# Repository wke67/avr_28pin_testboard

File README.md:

## AVR 28-Pin Test Board

The board can use a 300/400 mil ZIF socket for Mega AVR devices in dual inline package, eg. avr64dd28. All dx, ex 28-pin DIL devices have identical pin-out. The board provides:
- USB-C 12 Mbit interface
- dual UART interface for simultaneous serial and UPDI access.
- 3.3v, 500mA power supply from USB
- reset circuitry compatible with Arduino IDE and HV UPDI
- status LED on port PA6
- user switch on port PA7
- 32768 Hz crystal connected to PF0/PF1

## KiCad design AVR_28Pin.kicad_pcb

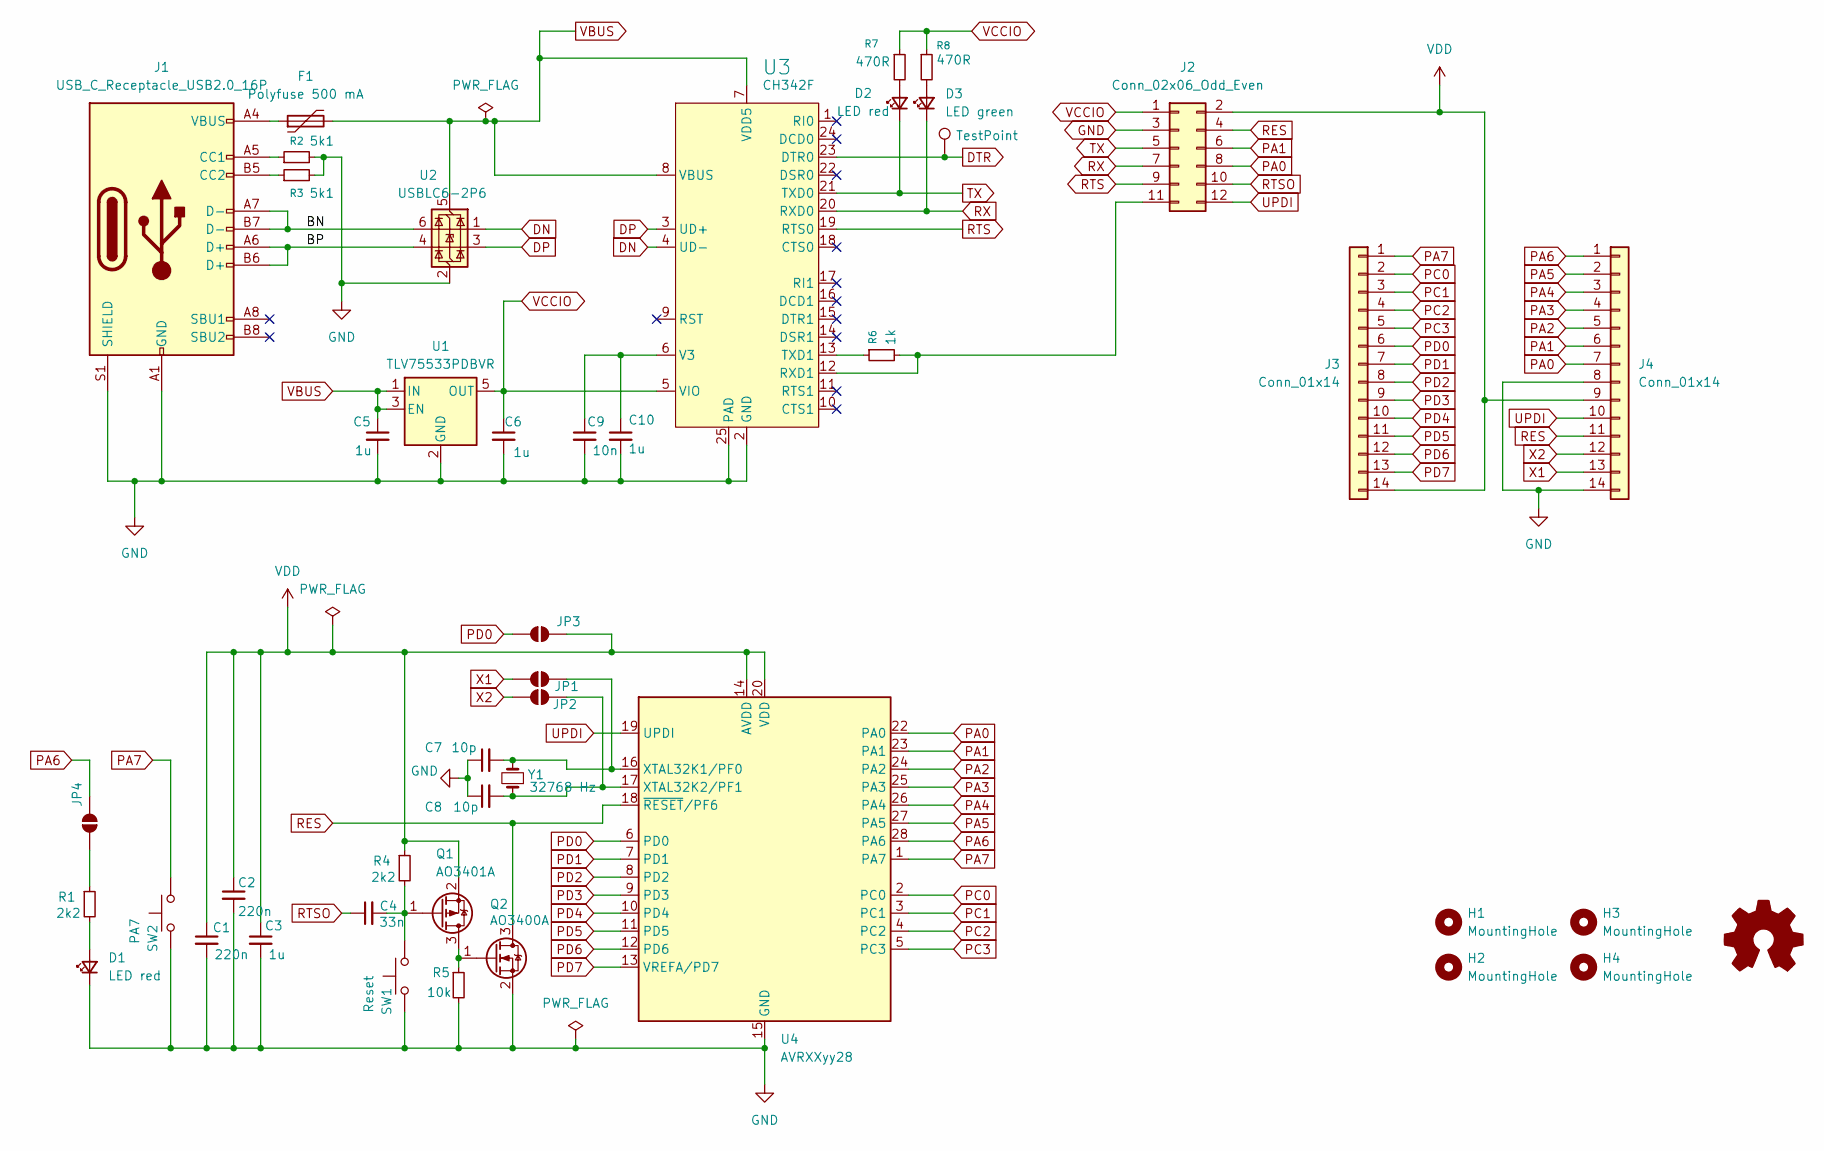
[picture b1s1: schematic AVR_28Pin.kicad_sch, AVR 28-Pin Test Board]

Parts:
C1, C2: 220n; C_0603_1608Metric; MPN CC0603KRX7R9BB224
C3, C5, C6, C10: 1u; C_0603_1608Metric; MPN CC0603KRX7R9BB105
C4: 33n; C_0603_1608Metric; MPN CC0603KRX7R9BB333
C7, C8: 10p; C_0603_1608Metric; MPN CC0402JRNPO9BN100
C9: 10n; C_0603_1608Metric; MPN CC0603KRX7R9BB103
D1: LED red; LED_0603_1608Metric; JLCPCB Part # C2286
D2: LED red; LED_0603_1608Metric; MPN LTST-C191KRKT; JLCPCB Part # C2286
D3: LED green; LED_0603_1608Metric; MPN LTST-C191KGKT
F1: Polyfuse 500 mA; Fuse_0805_2012Metric; MPN SMD0805P050TF; JLCPCB Part # C438897
H1, H2, H3, H4: MountingHole; MountingHole_3.2mm_M3_DIN965
J1: USB_C_Receptacle_USB2.0_16P; USB_C_Receptacle_GCT_USB4105-xx-A_16P_TopMnt_Horizontal; MPN USB-TYPE-C-16Pin female SMD right angle; JLCPCB Part # C393939
J2: Conn_02x06_Odd_Even; PinHeader_2x06_P2.54mm_Vertical; JLCPCB Part # C225521
J3, J4: Conn_01x14; PinHeader_1x14_P2.54mm_Vertical; JLCPCB Part # C2905490
JP1: PF2; SolderJumper-2_P1.3mm_Open_Pad1.0x1.5mm
JP2: PF1; SolderJumper-2_P1.3mm_Open_Pad1.0x1.5mm
JP3: MVIO; SolderJumper-2_P1.3mm_Open_Pad1.0x1.5mm
JP4: PA6; SolderJumper-2_P1.3mm_Open_Pad1.0x1.5mm
OHW1: Logo_Open_Hardware_Small; OSHW-Symbol_6.7x6mm_SilkScreen
Q1: AO3401A; SOT-23; MPN AO3401A
Q2: AO3400A; SOT-23; MPN AO3400A
R1, R4: 2k2; R_0603_1608Metric; MPN RC0603FR-072K2L
R2, R3: 5k1; R_0603_1608Metric; MPN RC0603FR-075K1L
R5: 10k; R_0603_1608Metric; MPN RC0603FR-0710KL
R6: 1k; R_0603_1608Metric; MPN RC0603FR-071KL
R7, R8: 470R; R_0603_1608Metric; MPN RC0603FR-07470RL
SW1: Reset; YTSA007A0151803B; JLCPCB Part # C2910660
SW2: PA7; YTSA007A0151803B; JLCPCB Part # C2910660
TP1: TestPoint; TestPoint_THTPad_2.0x2.0mm_Drill1.0mm
U1: TLV75533PDBVR; SOT-23-5; MPN TLV75533PDBVR
U2: USBLC6-2P6; SOT-666; MPN USBLC6-2P6; JLCPCB Part # C15999
U3: CH342F; QFN-24-1EP_4x4mm_P0.5mm_EP2.6x2.6mm; MPN CH342F
U4: AVRXXyy28; DIP_Socket-28_W7.62_3M_228-3341-00-0602J
Y1: 32768 Hz; Crystal_SMD_3215-2Pin_3.2x1.5mm; JLCPCB Part # C32346

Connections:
/BN: J1.A7 (D-), J1.B7 (D-), U2.6 (I/O1)
/BP: J1.A6 (D+), J1.B6 (D+), U2.4 (I/O2)
DN: U2.1 (I/O1), U3.4 (UD-)
DP: U2.3 (I/O2), U3.3 (UD+)
DTR: TP1.1, U3.23 (DTR0)
GND: C1.2, C2.2, C3.2, C5.2, C6.2, C7.1, C8.1, C9.2, C10.2, D1.1 (K), J1.A1 (GND), J1.A12 (GND), J1.B1 (GND), J1.B12 (GND), J1.S1 (SHIELD), J2.3, J4.8, J4.14, Q2.2 (S), R2.2, R3.2, R5.2, SW1.1, SW2.1, U1.2 (GND), U2.2 (GND), U3.2 (GND), U3.25 (PAD), U4.15 (GND), U4.21 (GND)
unnamed: D1.2 (A), R1.2
unnamed: D2.2 (A), R7.2
unnamed: D3.2 (A), R8.2
unnamed: F1.1, J1.A4 (VBUS), J1.A9 (VBUS), J1.B4 (VBUS), J1.B9 (VBUS)
unnamed: J1.A5 (CC1), R2.1
unnamed: J1.B5 (CC2), R3.1
unnamed: J2.11, R6.2, U3.12 (RXD1)
unnamed: C7.2, JP1.2 (B), U4.16 (XTAL32K1/PF0), Y1.2
unnamed: C8.2, JP2.2 (B), U4.17 (XTAL32K2/PF1), Y1.1
unnamed: JP4.2 (B), R1.1
unnamed: Q1.3 (D), Q2.1 (G), R5.1
unnamed: C4.2, Q1.1 (G), R4.2, SW1.2
unnamed: R6.1, U3.13 (TXD1)
unnamed: C9.1, C10.1, U3.6 (V3)
PA0: J2.8, J4.7, U4.22 (PA0)
PA1: J2.6, J4.6, U4.23 (PA1)
PA2: J4.5, U4.24 (PA2)
PA3: J4.4, U4.25 (PA3)
PA4: J4.3, U4.26 (PA4)
PA5: J4.2, U4.27 (PA5)
PA6: J4.1, JP4.1 (A), U4.28 (PA6)
PA7: J3.1, SW2.2, U4.1 (PA7)
PC0: J3.2, U4.2 (PC0)
PC1: J3.3, U4.3 (PC1)
PC2: J3.4, U4.4 (PC2)
PC3: J3.5, U4.5 (PC3)
PD0: J3.6, JP3.2 (B), U4.6 (PD0)
PD1: J3.7, U4.7 (PD1)
PD2: J3.8, U4.8 (PD2)
PD3: J3.9, U4.9 (PD3)
PD4: J3.10, U4.10 (PD4)
PD5: J3.11, U4.11 (PD5)
PD6: J3.12, U4.12 (PD6)
PD7: J3.13, U4.13 (VREFA/PD7)
RES: J2.4, J4.11, Q2.3 (D), U4.18 (~RESET/PF6)
RTS: J2.9, U3.19 (RTS0)
RTSO: C4.1, J2.10
RX: D3.1 (K), J2.7, U3.20 (RXD0)
TX: D2.1 (K), J2.5, U3.21 (TXD0)
UPDI: J2.12, J4.10, U4.19 (UPDI)
VBUS: C5.1, F1.2, U1.1 (IN), U1.3 (EN), U2.5 (VBUS), U3.7 (VDD5), U3.8 (VBUS)
VCCIO: C6.1, J2.1, R7.1, R8.1, U1.5 (OUT), U3.5 (VIO)
VDD: C1.1, C2.1, C3.1, J2.2, J3.14, J4.9, JP3.1 (A), Q1.2 (S), R4.1, U4.14 (AVDD), U4.20 (VDD)
X1: J4.13, JP1.1 (A)
X2: J4.12, JP2.1 (A)

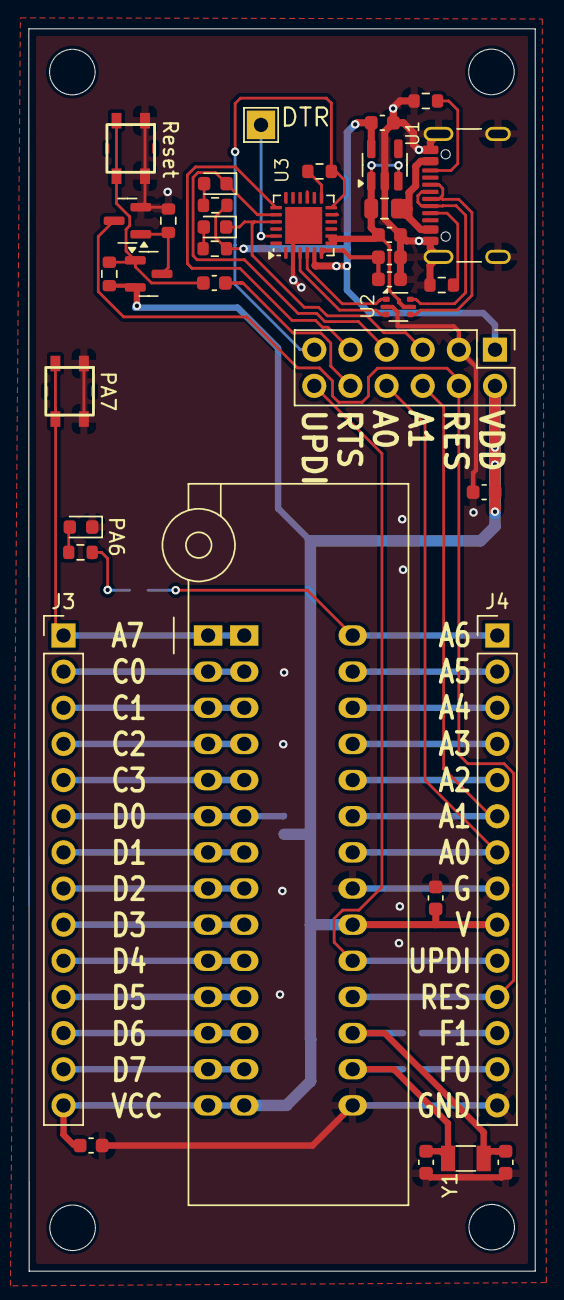
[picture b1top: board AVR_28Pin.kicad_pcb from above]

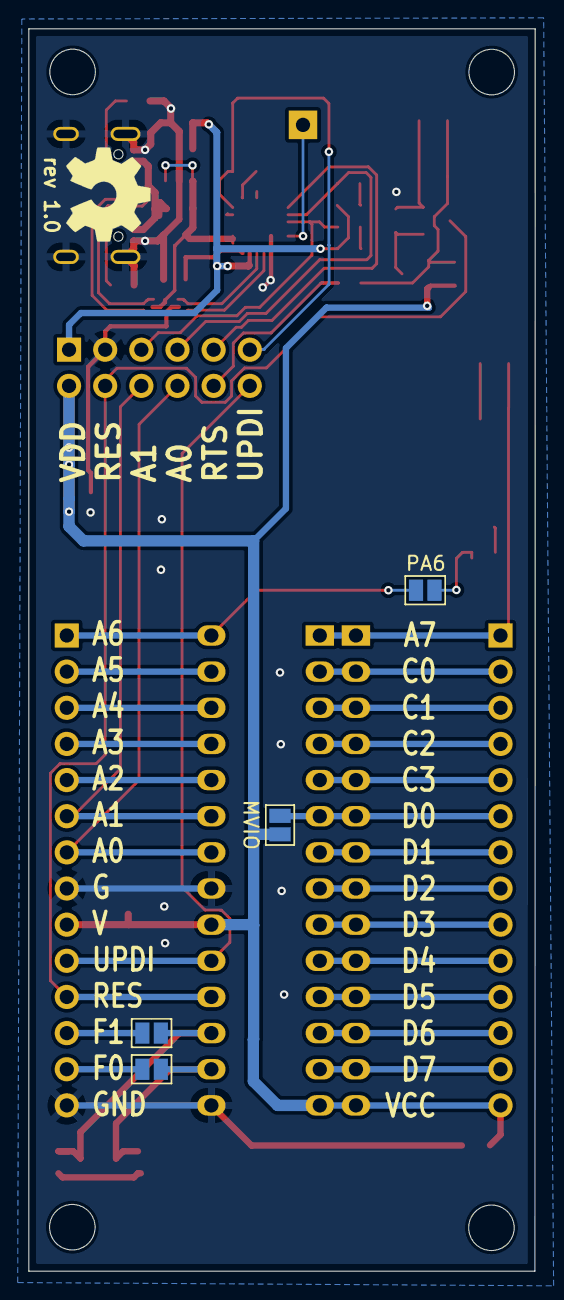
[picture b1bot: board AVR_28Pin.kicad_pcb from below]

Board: 2 copper layers, 35.6 x 87.3 mm, 45 parts (4 on the bottom side), 51 nets.

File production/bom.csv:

Designator,Footprint,Quantity,Value,LCSC Part #
"_14, _13, _12, _11, _10, _9, _8, _7, _6, _5, _4, _3, _2, ",,14,,
"C1, C2",0603,2,220n,CC0603KRX7R9BB224
"C10, C3, C5, C6",0603,4,1u,CC0603KRX7R9BB105
C4,0603,1,33n,CC0603KRX7R9BB333
"C7, C8",0603,2,10p,CC0402JRNPO9BN100
C9,0603,1,10n,CC0603KRX7R9BB103
"D1, D2",0603,2,LED red,C2286
D3,0603,1,LED green,LTST-C191KGKT
F1,0805,1,Polyfuse 500 mA,C438897
J1,USB_C_Receptacle_GCT_USB4105-xx-A_16P_TopMnt_Horizontal,1,USB_C_Receptacle_USB2.0_16P,C393939
J2,PinHeader_2x06_P2.54mm_Vertical,1,Conn_02x06_Odd_Even,C225521
"J3, J4",PinHeader_1x14_P2.54mm_Vertical,2,Conn_01x14,C2905490
Q1,SOT-23,1,AO3401A,AO3401A
Q2,SOT-23,1,AO3400A,AO3400A
"R1, R4",0603,2,2k2,RC0603FR-072K2L
"R2, R3",0603,2,5k1,RC0603FR-075K1L
R5,0603,1,10k,RC0603FR-0710KL
R6,0603,1,1k,RC0603FR-071KL
"R7, R8",0603,2,470R,RC0603FR-07470RL
SW1,YTSA007A0151803B,1,Reset,C2910660
SW2,YTSA007A0151803B,1,PA7,C2910660
TP1,TestPoint_THTPad_2.0x2.0mm_Drill1.0mm,1,TestPoint,
U1,SOT-23-5,1,TLV75533PDBVR,TLV75533PDBVR
U2,SOT-666,1,USBLC6-2P6,C15999
U3,QFN-24-1EP_4x4mm_P0.5mm_EP2.6x2.6mm,1,CH342F,CH342F
Y1,Crystal_SMD_3215-2Pin_3.2x1.5mm,1,32768 Hz,C32346
